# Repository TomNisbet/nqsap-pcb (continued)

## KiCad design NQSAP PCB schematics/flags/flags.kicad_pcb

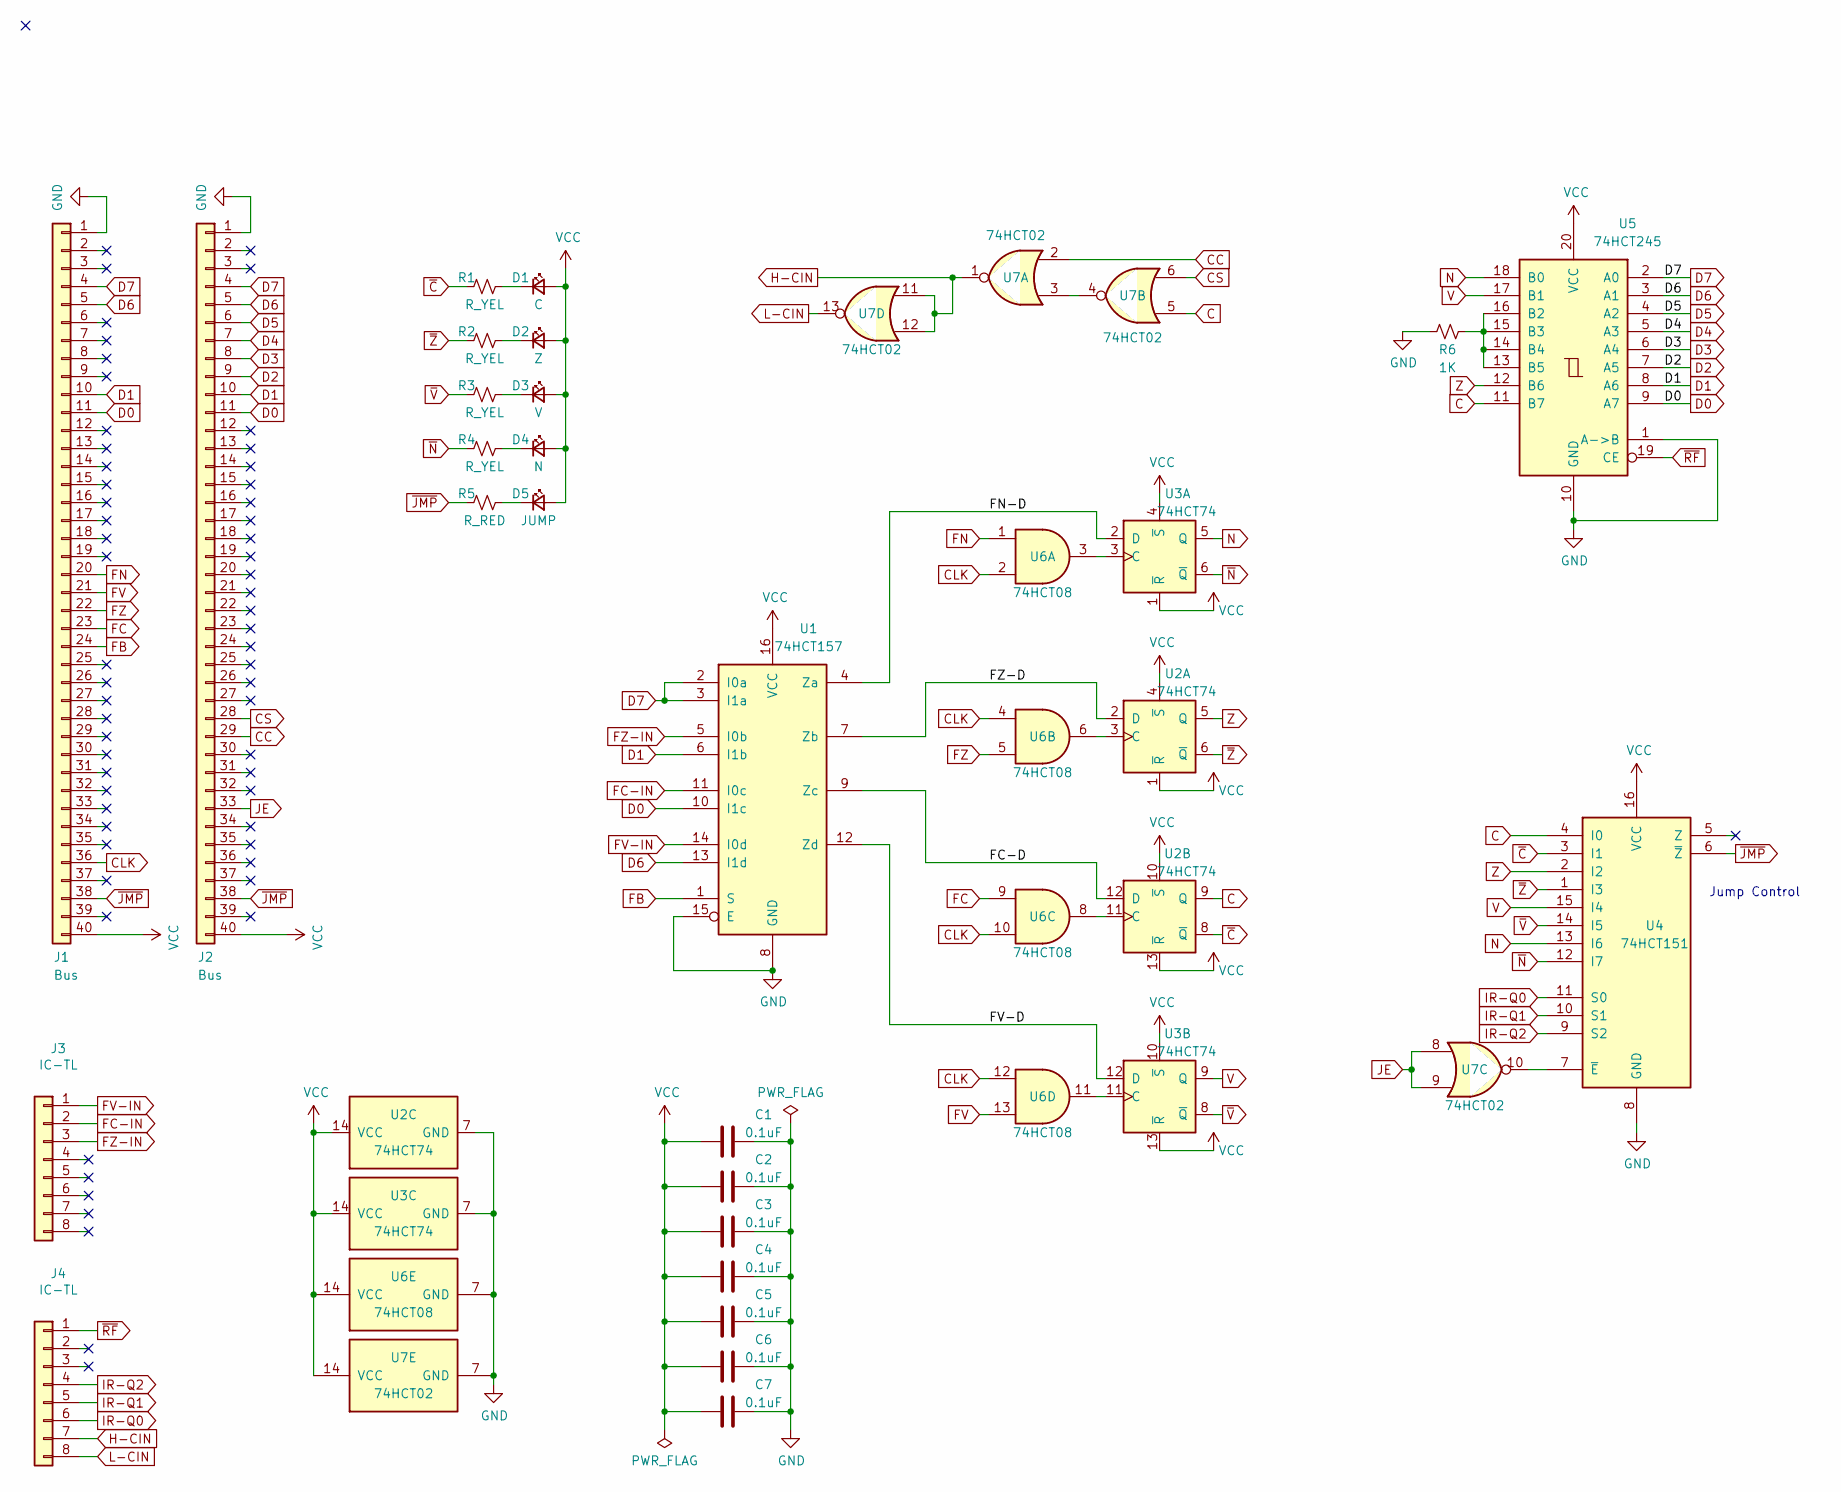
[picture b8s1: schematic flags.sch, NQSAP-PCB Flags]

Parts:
C1, C2, C3, C4, C5, C6, C7: 0.1uF; C_0805_2012Metric_Pad1.18x1.45mm_HandSolder
D1: C; LED_0805_2012Metric_Pad1.15x1.40mm_HandSolder
D2: Z; LED_0805_2012Metric_Pad1.15x1.40mm_HandSolder
D3: V; LED_0805_2012Metric_Pad1.15x1.40mm_HandSolder
D4: N; LED_0805_2012Metric_Pad1.15x1.40mm_HandSolder
D5: JUMP; LED_0805_2012Metric_Pad1.15x1.40mm_HandSolder
J1, J2: Bus; PinHeader_1x40_P2.54mm_Vertical
J3, J4: IC-TL; PinHeader_1x08_P2.54mm_Vertical
R1, R2, R3, R4: R_YEL; R_0805_2012Metric_Pad1.20x1.40mm_HandSolder
R5: R_RED; R_0805_2012Metric_Pad1.20x1.40mm_HandSolder
R6: 1K; R_0805_2012Metric_Pad1.20x1.40mm_HandSolder
U1: 74HCT157; DIP-16_W7.62mm
U2, U3: 74HCT74; DIP-14_W7.62mm
U4: 74HCT151; DIP-16_W7.62mm
U5: 74HCT245; DIP-20_W7.62mm
U6: 74HCT08; DIP-14_W7.62mm
U7: 74HCT02; DIP-14_W7.62mm

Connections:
/FC-D: U1.9 (Zc), U2.12 (D)
/FN-D: U1.4 (Za), U3.2 (D)
/FV-D: U1.12 (Zd), U3.12 (D)
/FZ-D: U1.7 (Zb), U2.2 (D)
C: U2.9 (Q), U4.4 (I0), U5.11 (B7), U7.5
CC: J2.29, U7.2
CLK: J1.36, U6.2, U6.4, U6.10, U6.12
CS: J2.28, U7.6
D0: J1.11, J2.11, U1.10 (I1c), U5.9 (A7)
D1: J1.10, J2.10, U1.6 (I1b), U5.8 (A6)
D2: J2.9, U5.7 (A5)
D3: J2.8, U5.6 (A4)
D4: J2.7, U5.5 (A3)
D5: J2.6, U5.4 (A2)
D6: J1.5, J2.5, U1.13 (I1d), U5.3 (A1)
D7: J1.4, J2.4, U1.2 (I0a), U1.3 (I1a), U5.2 (A0)
FB: J1.24, U1.1 (S)
FC: J1.23, U6.9
FC-IN: J3.2, U1.11 (I0c)
FN: J1.20, U6.1
FV: J1.21, U6.13
FV-IN: J3.1, U1.14 (I0d)
FZ: J1.22, U6.5
FZ-IN: J3.3, U1.5 (I0b)
GND: C1.1, C2.1, C3.1, C4.1, C5.1, C6.1, C7.1, J1.1, J2.1, R6.2, U1.8 (GND), U1.15 (E), U2.7 (GND), U3.7 (GND), U4.8 (GND), U5.1 (A->B), U5.10 (GND), U6.7 (GND), U7.7 (GND)
H-CIN: J4.7, U7.1, U7.11, U7.12
IR-Q0: J4.6, U4.11 (S0)
IR-Q1: J4.5, U4.10 (S1)
IR-Q2: J4.4, U4.9 (S2)
JE: J2.33, U7.8, U7.9
L-CIN: J4.8, U7.13
N: U3.5 (Q), U4.13 (I6), U5.18 (B0)
unnamed: D1.1 (K), R1.1
unnamed: D2.1 (K), R2.1
unnamed: D3.1 (K), R3.1
unnamed: D4.1 (K), R4.1
unnamed: D5.1 (K), R5.1
unnamed: R6.1, U5.13 (B5), U5.14 (B4), U5.15 (B3), U5.16 (B2)
unnamed: U2.3 (C), U6.6
unnamed: U2.11 (C), U6.8
unnamed: U3.3 (C), U6.3
unnamed: U3.11 (C), U6.11
unnamed: U4.7 (~E), U7.10
unnamed: U7.3, U7.4
V: U3.9 (Q), U4.15 (I4), U5.17 (B1)
VCC: C1.2, C2.2, C3.2, C4.2, C5.2, C6.2, C7.2, D1.2 (A), D2.2 (A), D3.2 (A), D4.2 (A), D5.2 (A), J1.40, J2.40, U1.16 (VCC), U2.1 (~R), U2.4 (~S), U2.10 (~S), U2.13 (~R), U2.14 (VCC), U3.1 (~R), U3.4 (~S), U3.10 (~S), U3.13 (~R), U3.14 (VCC), U4.16 (VCC), U5.20 (VCC), U6.14 (VCC), U7.14 (VCC)
Z: U2.5 (Q), U4.2 (I2), U5.12 (B6)
~C: R1.2, U2.8 (~Q), U4.3 (I1)
~JMP: J1.38, J2.38, R5.2, U4.6 (~Z)
~N: R4.2, U3.6 (~Q), U4.12 (I7)
~RF: J4.1, U5.19 (CE)
~V: R3.2, U3.8 (~Q), U4.14 (I5)
~Z: R2.2, U2.6 (~Q), U4.1 (I3)

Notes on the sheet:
Jump Control

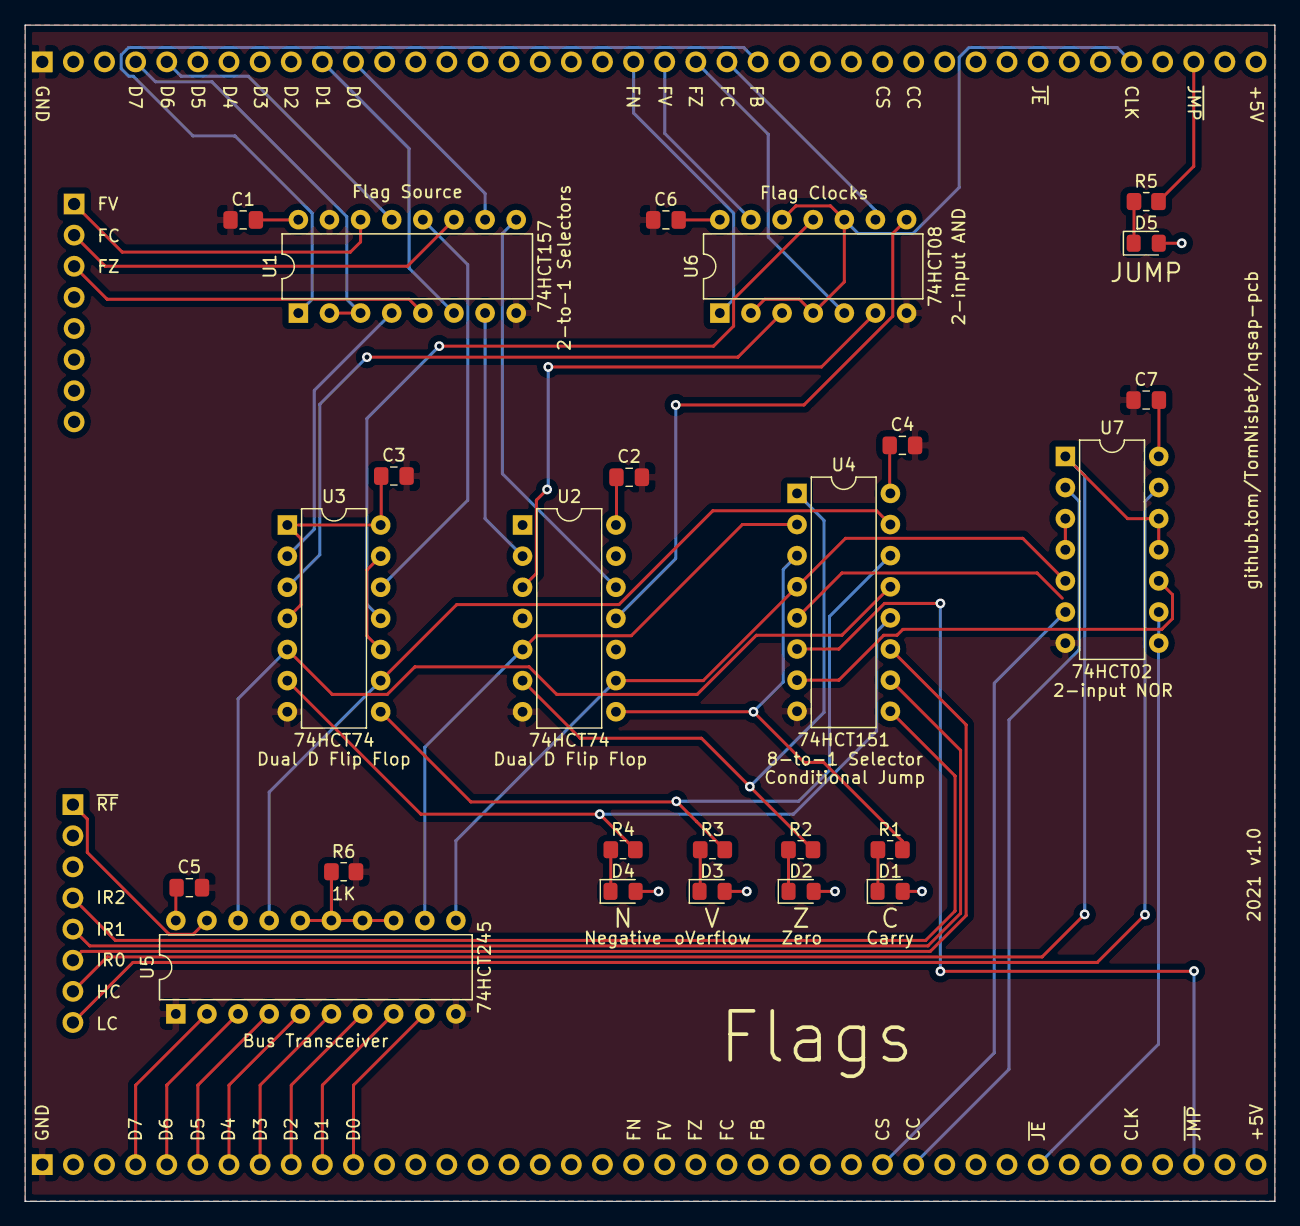
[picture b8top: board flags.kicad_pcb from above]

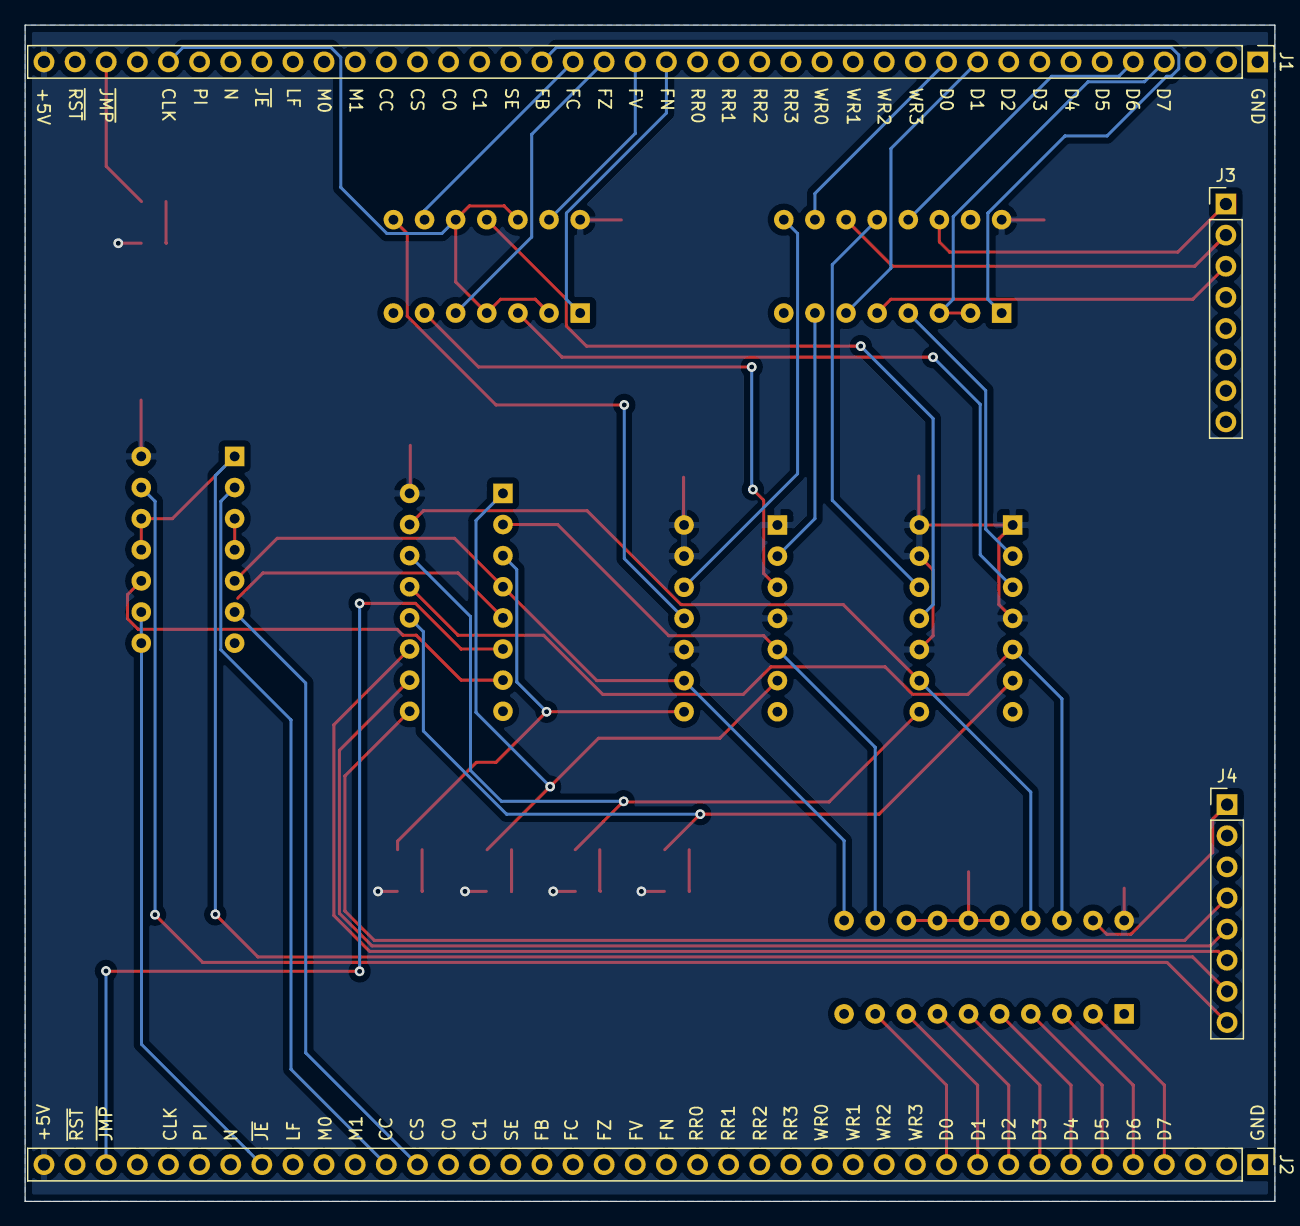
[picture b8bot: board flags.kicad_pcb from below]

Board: 2 copper layers, 102.0 x 96.0 mm, 29 parts (4 on the bottom side), 53 nets.

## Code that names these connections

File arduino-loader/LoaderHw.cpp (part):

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enum {
    PGM  = 10,   // OUTPUT - puts the host in PROGRAM mode
    LD2  = A0,   // OUTPUT - CLK the R2 register (register selects)
    SER  = A1,   // OUTPUT - Serial data to the R0/R1/R2 registers
    RCLK = A2,   // OUTPUT - output the values of all shift registers to the pins
    LD0  = A3,   // OUTPUT - CLK the R0 and R1 registers as 16 bits (control signals)
    RST  = A4,   // OUTPUT - drives the host RST line
    CLK  = A5    // OUTPUT - drives the host CLK line
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
    CTL_ALL_FLAGS = CTL_FN | CTL_FV | CTL_FZ | CTL_FC,

    CTL_C_ALU = 0,              // carry source ALU
    CTL_C_ALU_INV = CTL_C0,     // carry source ALU inverted
    CTL_C_SHIFT = CTL_C1,       // carry source Shift Register
    CTL_C_MASK = CTL_C0|CTL_C1, // all carry source bits
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    digitalWrite(LD0, LOW);     // Normally LOW, pulse HIGH to clock the R0/R1 registers
    pinMode(LD0, OUTPUT);
    digitalWrite(SER, LOW);     // Serial data to the shift registers
    pinMode(SER, OUTPUT);
    digitalWrite(RCLK, LOW);    // Normally LOW, pulse HIGH to put shift register data on the pins
    pinMode(RCLK, OUTPUT);
    digitalWrite(LD2, LOW);     // Normally LOW, pulse HIGH to clock the R2 register
    pinMode(LD2, OUTPUT);
    digitalWrite(PGM, HIGH);    // PGM is active LOW
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    return true;
}

bool LoaderHw::testAluOperation(uint8_t op, const char * opName, uint8_t a, uint8_t b, uint8_t carry) {
    char s[60];
    uint16_t readVal = aluCompute(op, a, b, carry);
    uint16_t expectedVal = localCompute(op, a, b, carry);
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
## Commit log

2021-09-25 initial REAME with bus drawings
2021-09-27 Finish routing of backplane
2021-09-27 add back view of backplane
2021-10-07 add kicad files
2021-10-12 more README details
2021-10-12 Add Microcode and IR/RC modules. Add clock circuit to Loader module.
2021-10-31 Add RAM, update and add gerbers for new boards
2021-11-08 arduino code for loader v2
2021-11-12 Initial documentation pages
2021-11-12 typos in docs
2021-11-12 doc pages for build1 and build2
2021-11-12 fix broken links
2021-11-13 documentation updates
2021-11-13 fix broken doc links
2021-11-13 more broken links
2021-11-13 update documentation home
2021-11-13 build1 doc updates
2021-11-13 Re-order documentation files
2021-11-18 update docs for build 2
2021-11-18 broken link
2021-11-18 build2 details
2021-11-22 update Loader/Debugger docs
2021-11-22 update IR docs
2021-11-22 remove duplicate doc file
2021-11-22 remove duplicate doc files
2021-11-22 system clock documentation
2021-11-23 add smaller inline photos for faster page load
2021-11-28 First set of microcode
2021-11-28 instruction set documentation
2021-11-28 update code link
2021-11-28 change filename to match docs
2021-11-28 move repo link to the bottom of the menu
2021-11-28 add text field to instruction set doc generator
2021-11-28 update register numbering
2021-12-07 updated KiCads and gerbers for the AB Registers and IR/RC module
2021-12-07 KiCad schematics, PCBs, and gerbers for the ALU and flags modules
2021-12-07 Loader and microcode updates for new ALU and flags modules
2021-12-18 fix typos in instruction set
2021-12-18 conditional jump error in microcode
2021-12-29 Loader and Microcode changes for build3
2021-12-29 documentaion updates for build 3
2021-12-29 documentation cleanup
2021-12-29 doc cleanup
2021-12-30 scematic images for alu and flags
2021-12-30 doc fixes - broken links
2021-12-30 docs - alu broken links
2021-12-30 nav test
2021-12-30 test docs
2021-12-30 docs test
2021-12-30 document 3rd set of boards
2021-12-30 broken doc links
2022-01-17 Update self test for new PC and SP
2022-01-18 schematics and layouts for build 4 (output, PC-SP)
2022-01-18 config files to normalize line endings
2022-01-18 normailize file line endings
2022-01-18 remove eol force in editorconfig
2022-07-24 Update RAM docs to better explain the memory segmentation
2022-07-25 doc updates to prep for build 4
2022-07-25 initial build 4 docs
2022-07-25 PC/SP doc updates
2022-07-25 update docs menu
2022-07-26 add build4 images to docs
2022-07-26 navigation and image errors in docs
2022-07-26 update flags docs
2022-07-26 build 4 docs
2022-07-29 document EEPROM glitch
2022-07-29 doc fixes
2022-07-29 fix timing diagrams
2022-07-29 update timing diagram
2022-07-29 docs fixes
2022-07-30 add to backplane and system docs
2022-07-31 Add register selects table to docs
2022-08-07 Add DXY register hardware self tests
2022-08-22 Add description of JSR to stack docs
2022-08-24 XY index adder docs
2022-08-24 dxy docs
2022-08-24 image link
2022-08-25 build5 gif added
2022-08-25 update home page with latest video
2022-08-25 image links
2022-09-29 docs add differences from NQSAP breadboard build
2024-07-27 update AB reg documentation
2024-09-06 add 39SF support for microcode sketch
2024-09-09 build 5 board updates
